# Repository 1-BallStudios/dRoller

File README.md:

# dRoller
A classic Dice Roller for TTRPG's like "Dungeons and Dragons" and "Dungeon Crawl Classics". Choose what dice and how many and roll them!
I actually cared about assembly this time, so you should be able to assemble it pretty easily. :)

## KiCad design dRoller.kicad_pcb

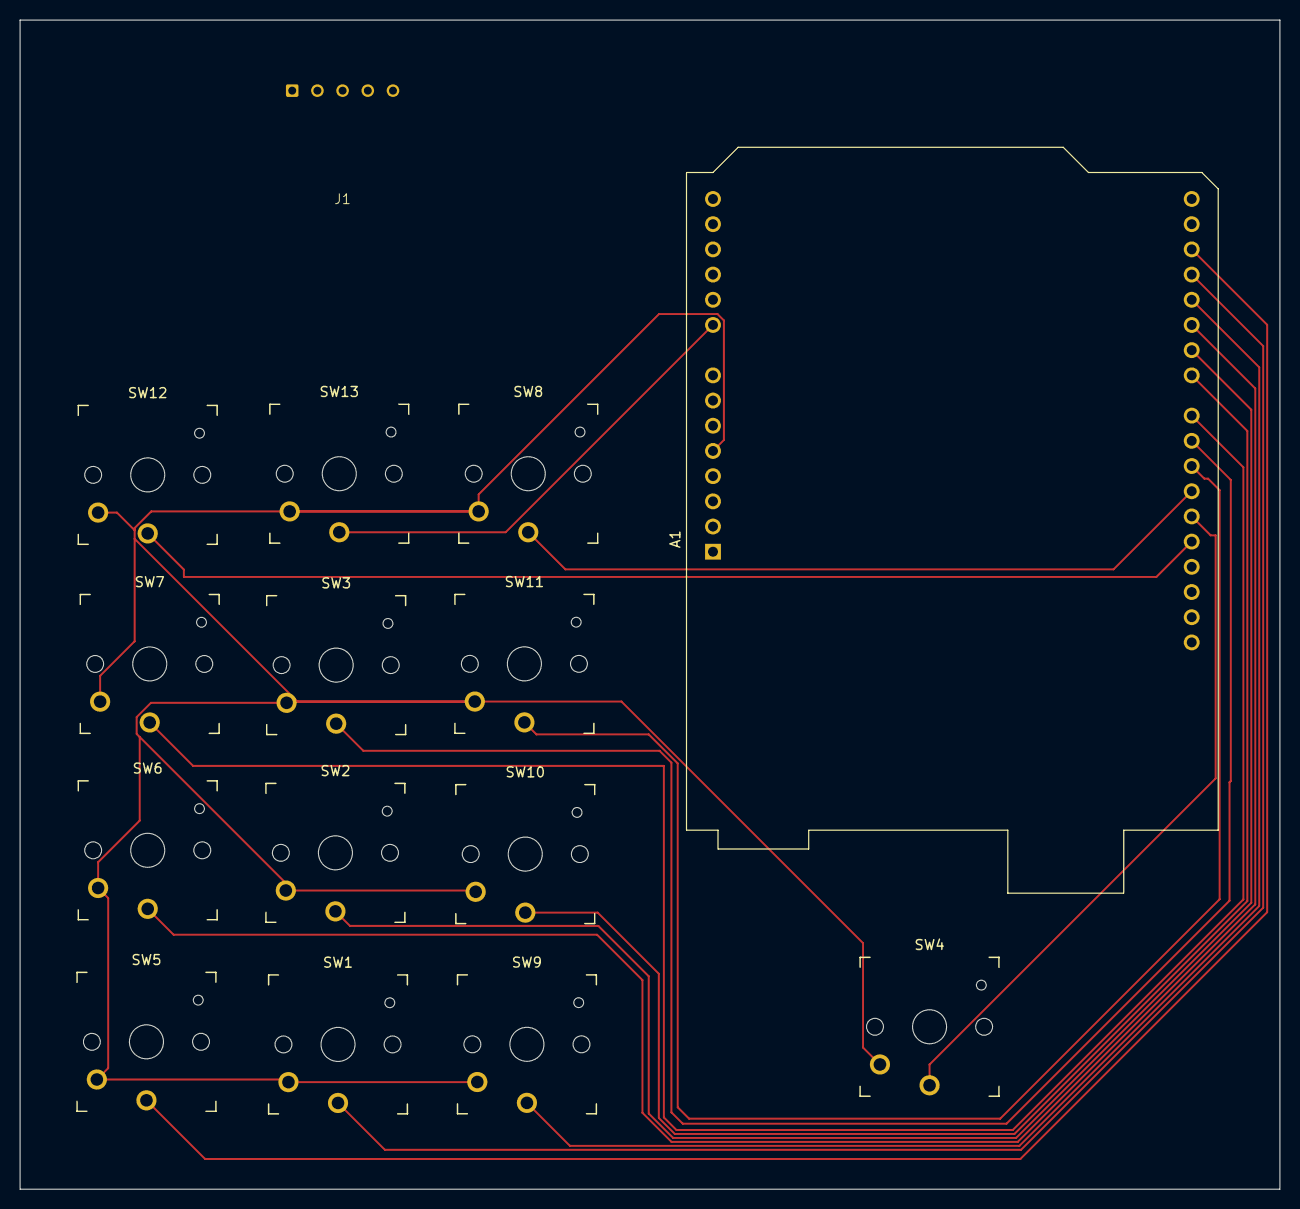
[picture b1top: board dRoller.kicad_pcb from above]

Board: 2 copper layers, 127.0 x 117.9 mm, 15 parts (0 on the bottom side), 14 nets.

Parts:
A1: Arduino_UNO_R3
J1: 14-Segment Display
SW1, SW2, SW3, SW4, SW5, SW6, SW7, SW8, SW9, SW10, SW11, SW12, SW13: SW_Push; Kailh Choc Low-Profile Switches

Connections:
+5V: A1.5 (+5V), SW1.2, SW2.2, SW3.2, SW4.2, SW5.2, SW6.2, SW7.2, SW8.2, SW9.2, SW10.2, SW11.2, SW12.2, SW13.2
/FATE: A1.25 (D10), SW11.1
/MINUS: A1.9 (A0), SW13.1
/NEXT: A1.26 (D11), SW8.1
/PLUS: A1.28 (D13), SW12.1
/ROLL: A1.27 (D12), SW4.1
/d2: A1.17 (D2), SW5.1
/d4: A1.18 (D3), SW1.1
/d6: A1.19 (D4), SW9.1
/d8: A1.20 (D5), SW6.1
/d10: A1.21 (D6), SW2.1
/d12: A1.22 (D7), SW10.1
/d20: A1.23 (D8), SW7.1
/d100: A1.24 (D9), SW3.1
